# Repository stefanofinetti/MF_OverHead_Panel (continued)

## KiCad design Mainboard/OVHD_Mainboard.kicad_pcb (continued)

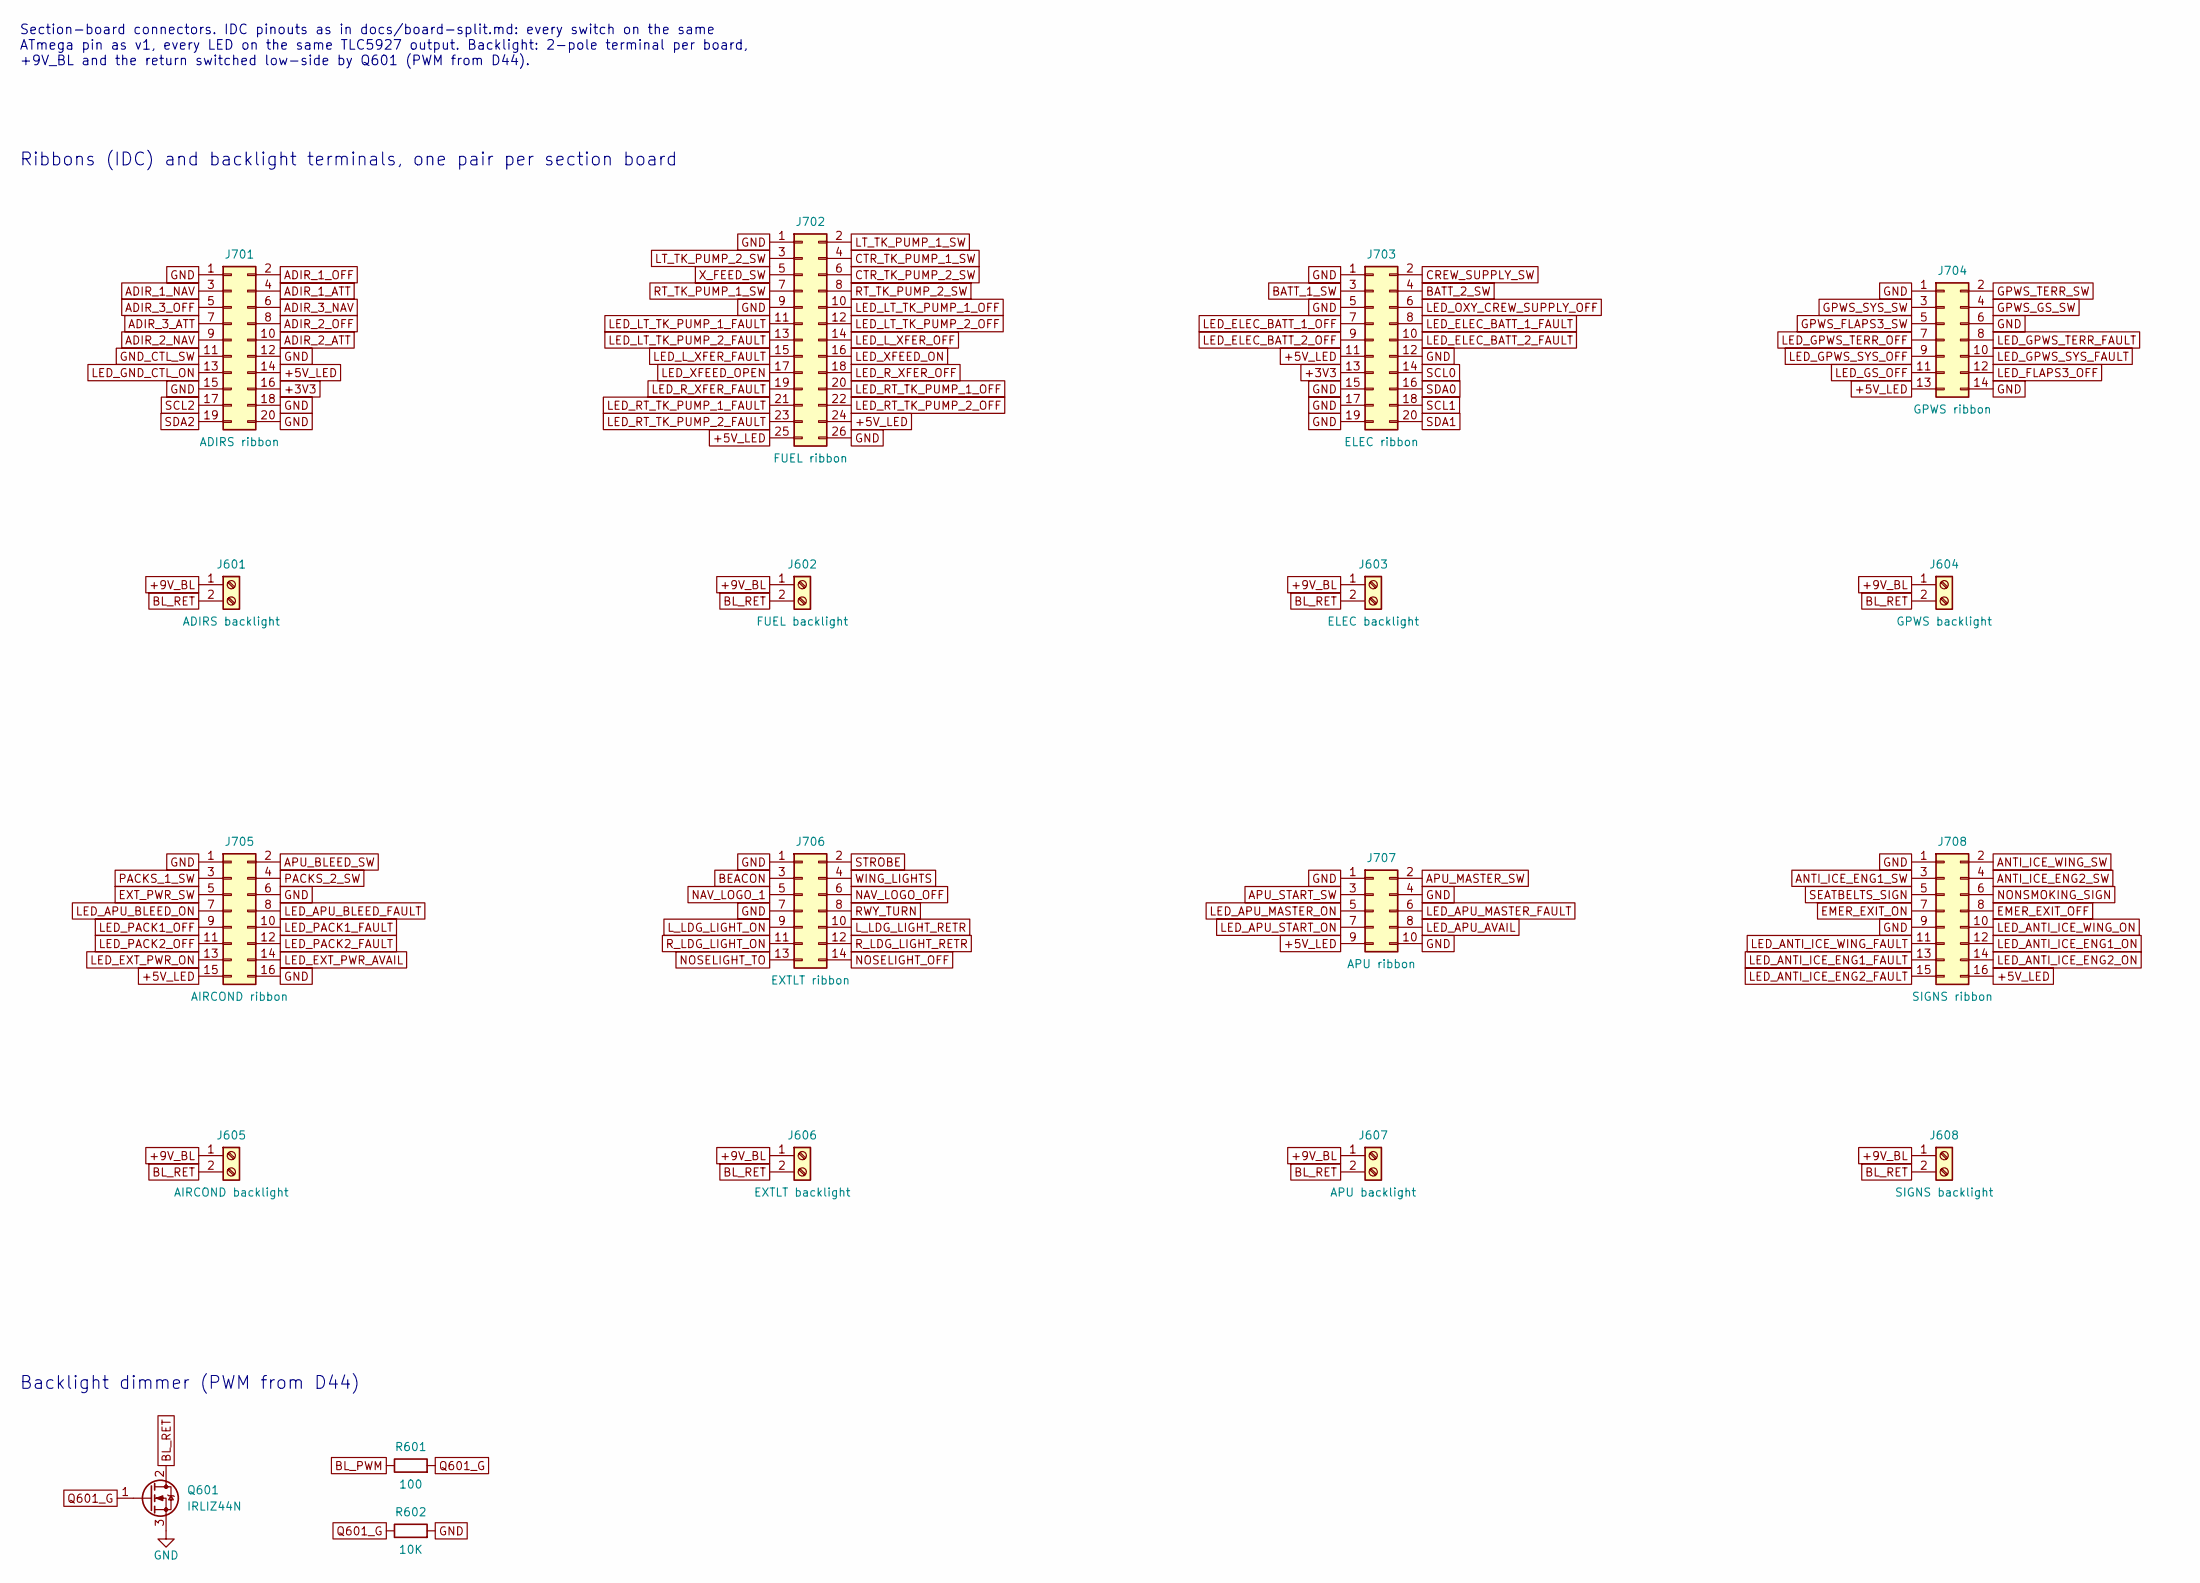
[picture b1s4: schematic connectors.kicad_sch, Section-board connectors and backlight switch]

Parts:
J601: ADIRS backlight; TerminalBlock_Phoenix_PT-1,5-2-3.5-H_1x02_P3.50mm_Horizontal
J602: FUEL backlight; TerminalBlock_Phoenix_PT-1,5-2-3.5-H_1x02_P3.50mm_Horizontal
J603: ELEC backlight; TerminalBlock_Phoenix_PT-1,5-2-3.5-H_1x02_P3.50mm_Horizontal
J604: GPWS backlight; TerminalBlock_Phoenix_PT-1,5-2-3.5-H_1x02_P3.50mm_Horizontal
J605: AIRCOND backlight; TerminalBlock_Phoenix_PT-1,5-2-3.5-H_1x02_P3.50mm_Horizontal
J606: EXTLT backlight; TerminalBlock_Phoenix_PT-1,5-2-3.5-H_1x02_P3.50mm_Horizontal
J607: APU backlight; TerminalBlock_Phoenix_PT-1,5-2-3.5-H_1x02_P3.50mm_Horizontal
J608: SIGNS backlight; TerminalBlock_Phoenix_PT-1,5-2-3.5-H_1x02_P3.50mm_Horizontal
J701: ADIRS ribbon; IDC-Header_2x10_P2.54mm_Vertical
J702: FUEL ribbon; IDC-Header_2x13_P2.54mm_Vertical
J703: ELEC ribbon; IDC-Header_2x10_P2.54mm_Vertical
J704: GPWS ribbon; IDC-Header_2x07_P2.54mm_Vertical
J705: AIRCOND ribbon; IDC-Header_2x08_P2.54mm_Vertical
J706: EXTLT ribbon; IDC-Header_2x07_P2.54mm_Vertical
J707: APU ribbon; IDC-Header_2x05_P2.54mm_Vertical
J708: SIGNS ribbon; IDC-Header_2x08_P2.54mm_Vertical
Q601: IRLIZ44N; TO-220F-3_Horizontal_TabDown
R601: 100; R_1206_3216Metric_Pad1.30x1.75mm_HandSolder
R602: 10K; R_1206_3216Metric_Pad1.30x1.75mm_HandSolder

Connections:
+3V3: J701.16, J703.13; also elsewhere on the board
+5V_LED: J701.14, J702.24, J702.25, J703.11, J704.13, J705.15, J707.9, J708.16; also elsewhere on the board
+9V_BL: J601.1, J602.1, J603.1, J604.1, J605.1, J606.1, J607.1, J608.1; also elsewhere on the board
ADIR_1_ATT: J701.4; also elsewhere on the board
ADIR_1_NAV: J701.3; also elsewhere on the board
ADIR_1_OFF: J701.2; also elsewhere on the board
ADIR_2_ATT: J701.10; also elsewhere on the board
ADIR_2_NAV: J701.9; also elsewhere on the board
ADIR_2_OFF: J701.8; also elsewhere on the board
ADIR_3_ATT: J701.7; also elsewhere on the board
ADIR_3_NAV: J701.6; also elsewhere on the board
ADIR_3_OFF: J701.5; also elsewhere on the board
ANTI_ICE_ENG1_SW: J708.3; also elsewhere on the board
ANTI_ICE_ENG2_SW: J708.4; also elsewhere on the board
ANTI_ICE_WING_SW: J708.2; also elsewhere on the board
APU_BLEED_SW: J705.2; also elsewhere on the board
APU_MASTER_SW: J707.2; also elsewhere on the board
APU_START_SW: J707.3; also elsewhere on the board
BATT_1_SW: J703.3; also elsewhere on the board
BATT_2_SW: J703.4; also elsewhere on the board
BEACON: J706.3; also elsewhere on the board
BL_PWM: R601.1; also elsewhere on the board
BL_RET: J601.2, J602.2, J603.2, J604.2, J605.2, J606.2, J607.2, J608.2, Q601.2 (D)
CREW_SUPPLY_SW: J703.2; also elsewhere on the board
CTR_TK_PUMP_1_SW: J702.4; also elsewhere on the board
CTR_TK_PUMP_2_SW: J702.6; also elsewhere on the board
EMER_EXIT_OFF: J708.8; also elsewhere on the board
EMER_EXIT_ON: J708.7; also elsewhere on the board
EXT_PWR_SW: J705.5; also elsewhere on the board
GND: J701.1, J701.12, J701.15, J701.18, J701.20, J702.1, J702.9, J702.26, J703.1, J703.5, J703.12, J703.15, J703.17, J703.19, J704.1, J704.6, J704.14, J705.1, J705.6, J705.16, J706.1, J706.7, J707.1, J707.4, J707.10, J708.1, J708.9, Q601.3 (S), R602.2; also elsewhere on the board
GND_CTL_SW: J701.11; also elsewhere on the board
GPWS_FLAPS3_SW: J704.5; also elsewhere on the board
GPWS_GS_SW: J704.4; also elsewhere on the board
GPWS_SYS_SW: J704.3; also elsewhere on the board
GPWS_TERR_SW: J704.2; also elsewhere on the board
LED_ANTI_ICE_ENG1_FAULT: J708.13; also elsewhere on the board
LED_ANTI_ICE_ENG1_ON: J708.12; also elsewhere on the board
LED_ANTI_ICE_ENG2_FAULT: J708.15; also elsewhere on the board
LED_ANTI_ICE_ENG2_ON: J708.14; also elsewhere on the board
LED_ANTI_ICE_WING_FAULT: J708.11; also elsewhere on the board
LED_ANTI_ICE_WING_ON: J708.10; also elsewhere on the board
LED_APU_AVAIL: J707.8; also elsewhere on the board
LED_APU_BLEED_FAULT: J705.8; also elsewhere on the board
LED_APU_BLEED_ON: J705.7; also elsewhere on the board
LED_APU_MASTER_FAULT: J707.6; also elsewhere on the board
LED_APU_MASTER_ON: J707.5; also elsewhere on the board
LED_APU_START_ON: J707.7; also elsewhere on the board
LED_ELEC_BATT_1_FAULT: J703.8; also elsewhere on the board
LED_ELEC_BATT_1_OFF: J703.7; also elsewhere on the board
LED_ELEC_BATT_2_FAULT: J703.10; also elsewhere on the board
LED_ELEC_BATT_2_OFF: J703.9; also elsewhere on the board
LED_EXT_PWR_AVAIL: J705.14; also elsewhere on the board
LED_EXT_PWR_ON: J705.13; also elsewhere on the board
LED_FLAPS3_OFF: J704.12; also elsewhere on the board
LED_GND_CTL_ON: J701.13; also elsewhere on the board
LED_GPWS_SYS_FAULT: J704.10; also elsewhere on the board
LED_GPWS_SYS_OFF: J704.9; also elsewhere on the board
LED_GPWS_TERR_FAULT: J704.8; also elsewhere on the board
LED_GPWS_TERR_OFF: J704.7; also elsewhere on the board
LED_GS_OFF: J704.11; also elsewhere on the board
LED_LT_TK_PUMP_1_FAULT: J702.11; also elsewhere on the board
LED_LT_TK_PUMP_1_OFF: J702.10; also elsewhere on the board
LED_LT_TK_PUMP_2_FAULT: J702.13; also elsewhere on the board
LED_LT_TK_PUMP_2_OFF: J702.12; also elsewhere on the board
LED_L_XFER_FAULT: J702.15; also elsewhere on the board
LED_L_XFER_OFF: J702.14; also elsewhere on the board
LED_OXY_CREW_SUPPLY_OFF: J703.6; also elsewhere on the board
LED_PACK1_FAULT: J705.10; also elsewhere on the board
LED_PACK1_OFF: J705.9; also elsewhere on the board
LED_PACK2_FAULT: J705.12; also elsewhere on the board
LED_PACK2_OFF: J705.11; also elsewhere on the board
LED_RT_TK_PUMP_1_FAULT: J702.21; also elsewhere on the board
LED_RT_TK_PUMP_1_OFF: J702.20; also elsewhere on the board
LED_RT_TK_PUMP_2_FAULT: J702.23; also elsewhere on the board
LED_RT_TK_PUMP_2_OFF: J702.22; also elsewhere on the board
LED_R_XFER_FAULT: J702.19; also elsewhere on the board
LED_R_XFER_OFF: J702.18; also elsewhere on the board
LED_XFEED_ON: J702.16; also elsewhere on the board
LED_XFEED_OPEN: J702.17; also elsewhere on the board
LT_TK_PUMP_1_SW: J702.2; also elsewhere on the board
LT_TK_PUMP_2_SW: J702.3; also elsewhere on the board
L_LDG_LIGHT_ON: J706.9; also elsewhere on the board
L_LDG_LIGHT_RETR: J706.10; also elsewhere on the board
NAV_LOGO_1: J706.5; also elsewhere on the board
NAV_LOGO_OFF: J706.6; also elsewhere on the board
NONSMOKING_SIGN: J708.6; also elsewhere on the board
NOSELIGHT_OFF: J706.14; also elsewhere on the board
NOSELIGHT_TO: J706.13; also elsewhere on the board
PACKS_1_SW: J705.3; also elsewhere on the board
PACKS_2_SW: J705.4; also elsewhere on the board
Q601_G: Q601.1 (G), R601.2, R602.1
RT_TK_PUMP_1_SW: J702.7; also elsewhere on the board
RT_TK_PUMP_2_SW: J702.8; also elsewhere on the board
RWY_TURN: J706.8; also elsewhere on the board
R_LDG_LIGHT_ON: J706.11; also elsewhere on the board
R_LDG_LIGHT_RETR: J706.12; also elsewhere on the board
SCL0: J703.14; also elsewhere on the board
SCL1: J703.18; also elsewhere on the board
SCL2: J701.17; also elsewhere on the board
SDA0: J703.16; also elsewhere on the board
SDA1: J703.20; also elsewhere on the board
SDA2: J701.19; also elsewhere on the board
SEATBELTS_SIGN: J708.5; also elsewhere on the board
STROBE: J706.2; also elsewhere on the board
WING_LIGHTS: J706.4; also elsewhere on the board
X_FEED_SW: J702.5; also elsewhere on the board

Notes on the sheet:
Ribbons (IDC) and backlight terminals, one pair per section board
Section-board connectors. IDC pinouts as in docs/board-split.md: every switch on the same ATmega pin as v1, every LED on the same TLC5927 output. Backlight: 2-pole terminal per board, +9V_BL and the return switched low-side by Q601 (PWM from D44).
Backlight dimmer (PWM from D44)

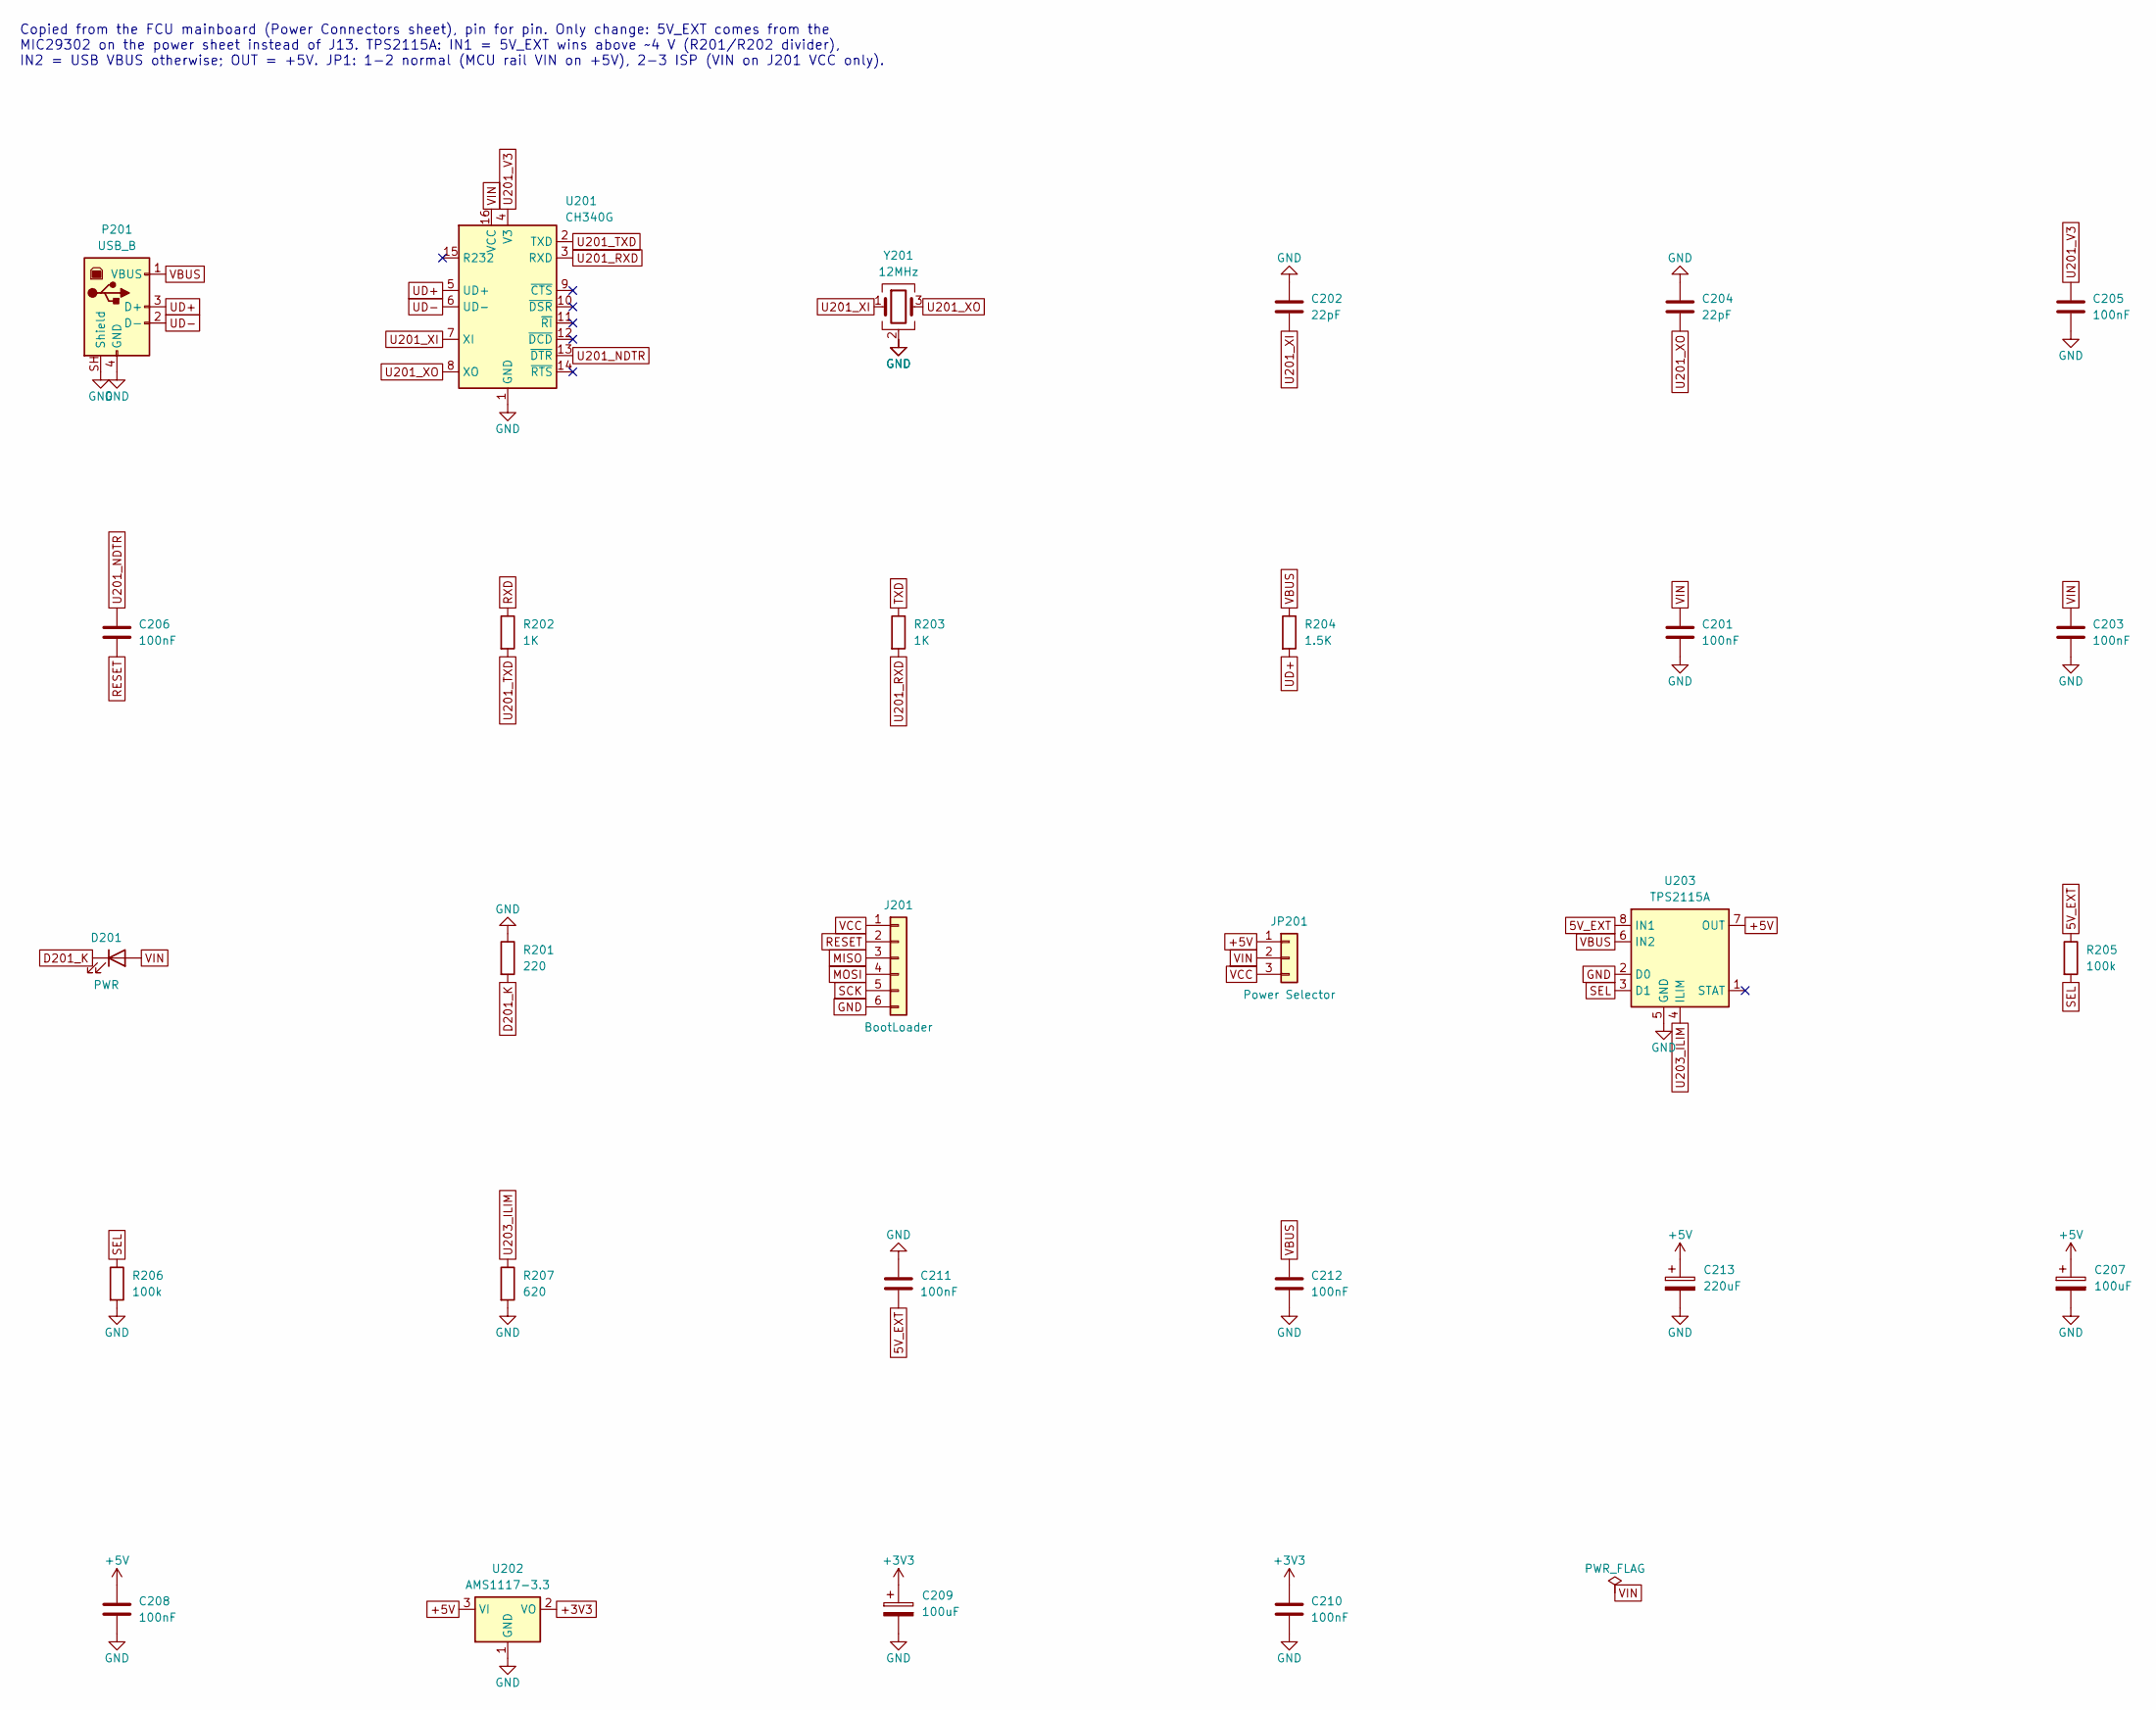
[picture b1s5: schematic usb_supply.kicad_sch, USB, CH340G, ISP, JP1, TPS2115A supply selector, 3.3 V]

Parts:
C201, C203, C205, C206, C208, C210, C211, C212: 100nF; C_1206_3216Metric_Pad1.33x1.80mm_HandSolder
C202, C204: 22pF; C_1206_3216Metric_Pad1.33x1.80mm_HandSolder
C207, C209: 100uF; C_Elec_6.3x7.7
C213: 220uF; C_Elec_6.3x7.7
D201: PWR; LED_1206_3216Metric_Pad1.42x1.75mm_HandSolder
J201: BootLoader; PinHeader_1x06_P2.54mm_Vertical
JP201: Power Selector; PinHeader_1x03_P2.54mm_Vertical
P201: USB_B; USB_B_OST_USB-B1HSxx_Horizontal
R201: 220; R_1206_3216Metric_Pad1.30x1.75mm_HandSolder
R202, R203: 1K; R_1206_3216Metric_Pad1.30x1.75mm_HandSolder
R204: 1.5K; R_1206_3216Metric_Pad1.30x1.75mm_HandSolder
R205, R206: 100k; R_1206_3216Metric_Pad1.30x1.75mm_HandSolder
R207: 620; R_1206_3216Metric_Pad1.30x1.75mm_HandSolder
U201: CH340G; SOIC-16_3.9x9.9mm_P1.27mm
U202: AMS1117-3.3; SOT-223-3_TabPin2
U203: TPS2115A; TSSOP-8_4.4x3mm_P0.65mm
Y201: 12MHz; Crystal_SMD_EuroQuartz_MQ-4Pin_7.0x5.0mm_HandSoldering

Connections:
5V_EXT: C211.2, R205.1, U203.8 (IN1); also elsewhere on the board
+3V3: C209.1, C210.1, U202.2 (VO); also elsewhere on the board
+5V: C207.1, C208.1, C213.1, JP201.1, U202.3 (VI), U203.7 (OUT); also elsewhere on the board
D201_K: D201.1 (K), R201.2
GND: C201.2, C202.1, C203.2, C204.1, C205.2, C207.2, C208.2, C209.2, C210.2, C211.1, C212.2, C213.2, J201.6, P201.4 (GND), P201.SH (Shield), R201.1, R206.2, R207.2, U201.1 (GND), U202.1 (GND), U203.2 (D0), U203.5 (GND), Y201.2 (G), Y201.4 (G); also elsewhere on the board
MISO: J201.3; also elsewhere on the board
MOSI: J201.4; also elsewhere on the board
RESET: C206.2, J201.2; also elsewhere on the board
RXD: R202.1; also elsewhere on the board
SCK: J201.5; also elsewhere on the board
SEL: R205.2, R206.1, U203.3 (D1)
TXD: R203.1; also elsewhere on the board
U201_NDTR: C206.1, U201.13 (~DTR)
U201_RXD: R203.2, U201.3 (RXD)
U201_TXD: R202.2, U201.2 (TXD)
U201_V3: C205.1, U201.4 (V3)
U201_XI: C202.2, U201.7 (XI), Y201.1
U201_XO: C204.2, U201.8 (XO), Y201.3
U203_ILIM: R207.1, U203.4 (ILIM)
UD+: P201.3 (D+), R204.2, U201.5 (UD+)
UD-: P201.2 (D-), U201.6 (UD-)
VBUS: C212.1, P201.1 (VBUS), R204.1, U203.6 (IN2)
VCC: J201.1, JP201.3
VIN: C201.1, C203.1, D201.2 (A), JP201.2, U201.16 (VCC); also elsewhere on the board

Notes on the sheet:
Copied from the FCU mainboard (Power Connectors sheet), pin for pin. Only change: 5V_EXT comes from the MIC29302 on the power sheet instead of J13. TPS2115A: IN1 = 5V_EXT wins above ~4 V (R201/R202 divider), IN2 = USB VBUS otherwise; OUT = +5V. JP1: 1-2 normal (MCU rail VIN on +5V), 2-3 ISP (VIN on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

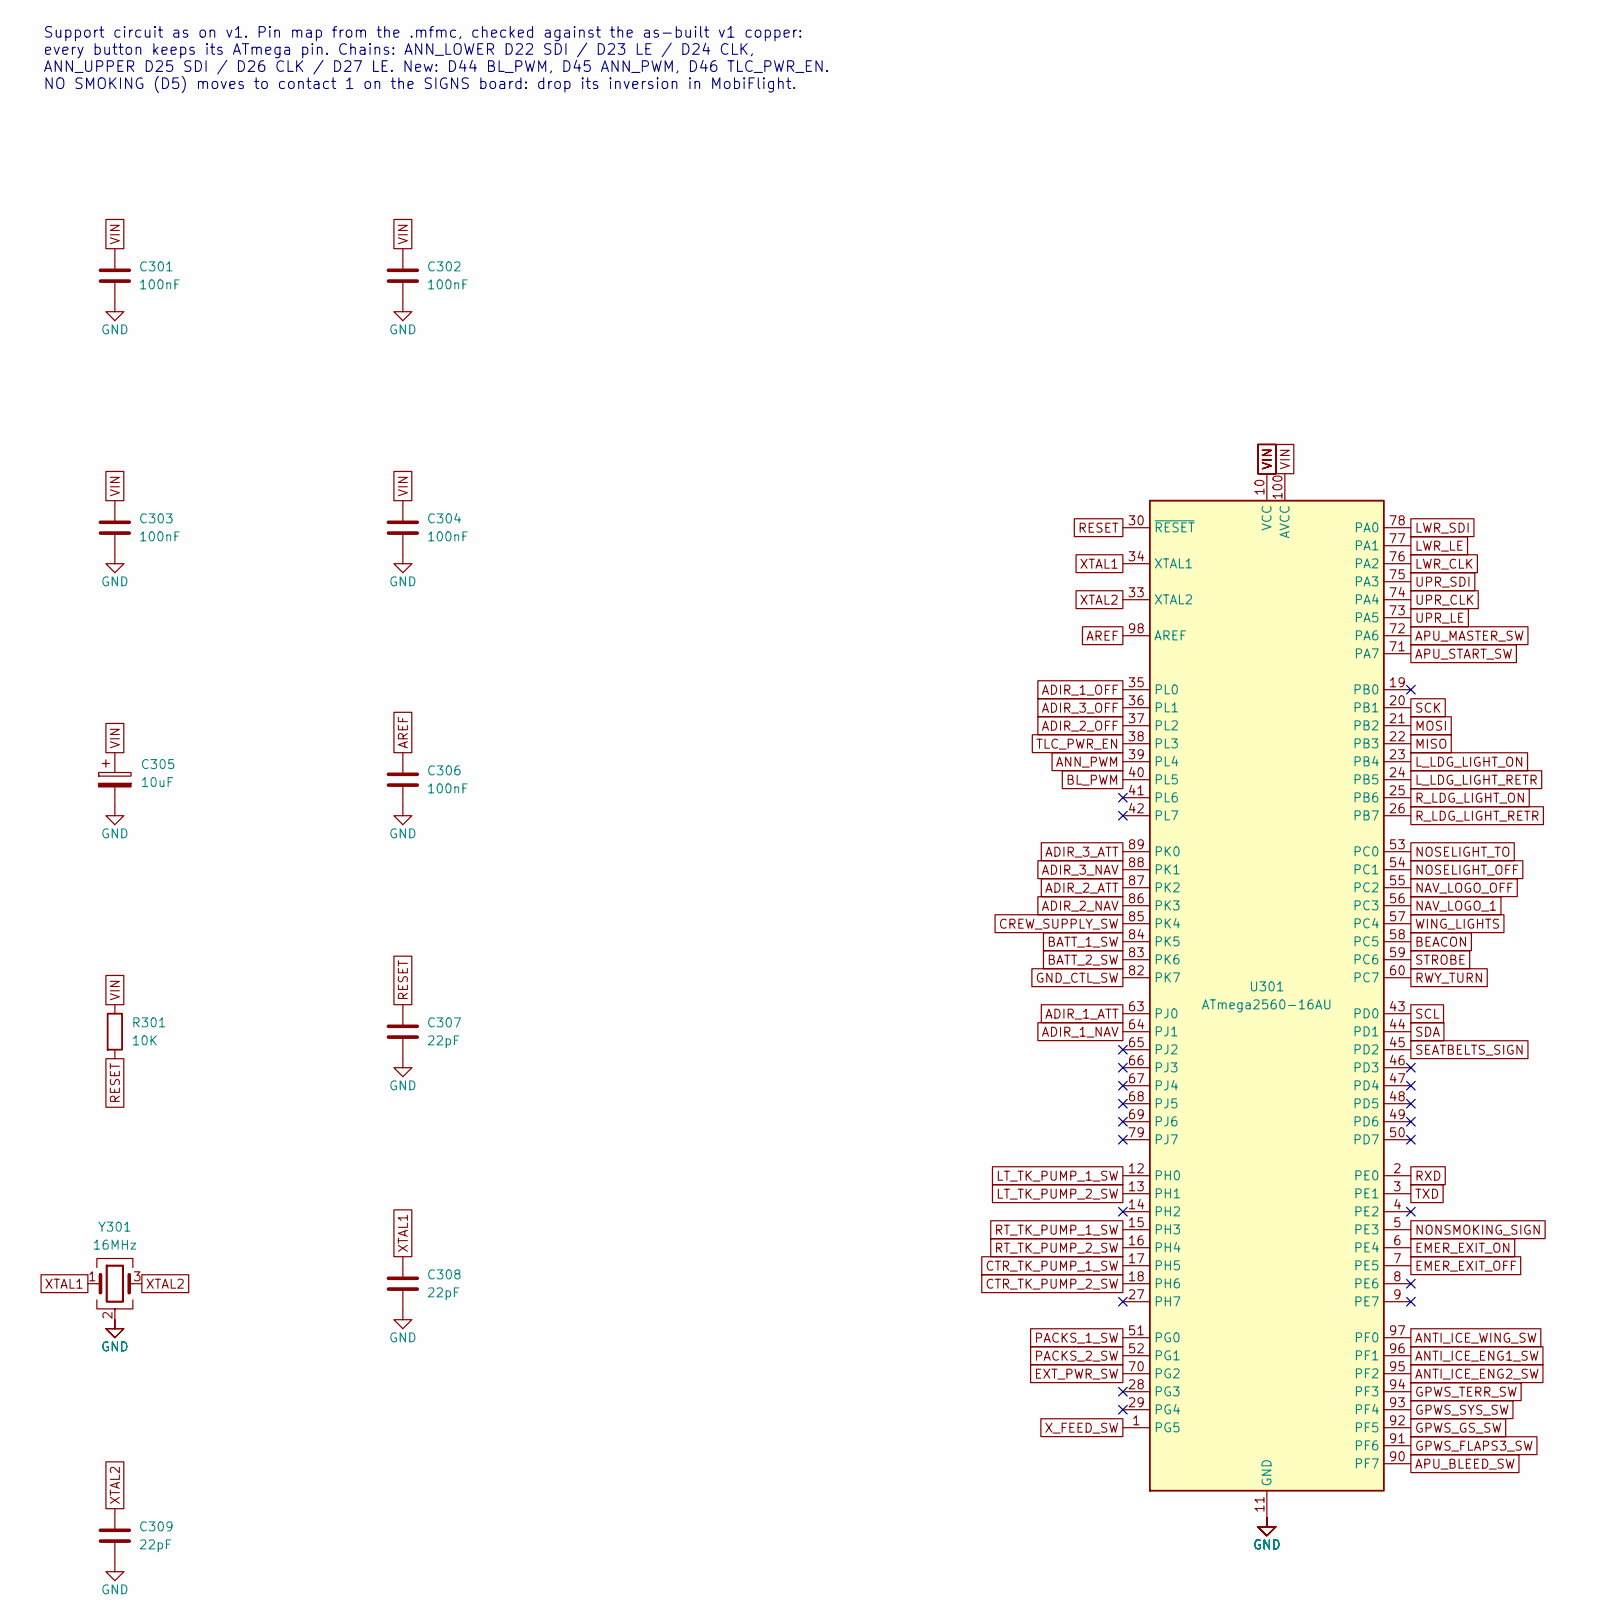
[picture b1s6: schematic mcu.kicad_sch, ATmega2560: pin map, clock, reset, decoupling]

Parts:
C301, C302, C303, C304, C306: 100nF; C_1206_3216Metric_Pad1.33x1.80mm_HandSolder
C305: 10uF; CP_Elec_4x5.4
C307, C308, C309: 22pF; C_1206_3216Metric_Pad1.33x1.80mm_HandSolder
R301: 10K; R_1206_3216Metric_Pad1.30x1.75mm_HandSolder
U301: ATmega2560-16AU; TQFP-100_14x14mm_P0.5mm
Y301: 16MHz; Crystal_SMD_EuroQuartz_MQ-4Pin_7.0x5.0mm_HandSoldering

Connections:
ADIR_1_ATT: U301.63 (PJ0); also elsewhere on the board
ADIR_1_NAV: U301.64 (PJ1); also elsewhere on the board
ADIR_1_OFF: U301.35 (PL0); also elsewhere on the board
ADIR_2_ATT: U301.87 (PK2); also elsewhere on the board
ADIR_2_NAV: U301.86 (PK3); also elsewhere on the board
ADIR_2_OFF: U301.37 (PL2); also elsewhere on the board
ADIR_3_ATT: U301.89 (PK0); also elsewhere on the board
ADIR_3_NAV: U301.88 (PK1); also elsewhere on the board
ADIR_3_OFF: U301.36 (PL1); also elsewhere on the board
ANN_PWM: U301.39 (PL4); also elsewhere on the board
ANTI_ICE_ENG1_SW: U301.96 (PF1); also elsewhere on the board
ANTI_ICE_ENG2_SW: U301.95 (PF2); also elsewhere on the board
ANTI_ICE_WING_SW: U301.97 (PF0); also elsewhere on the board
APU_BLEED_SW: U301.90 (PF7); also elsewhere on the board
APU_MASTER_SW: U301.72 (PA6); also elsewhere on the board
APU_START_SW: U301.71 (PA7); also elsewhere on the board
AREF: C306.1, U301.98 (AREF)
BATT_1_SW: U301.84 (PK5); also elsewhere on the board
BATT_2_SW: U301.83 (PK6); also elsewhere on the board
BEACON: U301.58 (PC5); also elsewhere on the board
BL_PWM: U301.40 (PL5); also elsewhere on the board
CREW_SUPPLY_SW: U301.85 (PK4); also elsewhere on the board
CTR_TK_PUMP_1_SW: U301.17 (PH5); also elsewhere on the board
CTR_TK_PUMP_2_SW: U301.18 (PH6); also elsewhere on the board
EMER_EXIT_OFF: U301.7 (PE5); also elsewhere on the board
EMER_EXIT_ON: U301.6 (PE4); also elsewhere on the board
EXT_PWR_SW: U301.70 (PG2); also elsewhere on the board
GND: C301.2, C302.2, C303.2, C304.2, C305.2, C306.2, C307.2, C308.2, C309.2, U301.11 (GND), U301.32 (GND), U301.62 (GND), U301.81 (GND), U301.99 (GND), Y301.2 (G), Y301.4 (G); also elsewhere on the board
GND_CTL_SW: U301.82 (PK7); also elsewhere on the board
GPWS_FLAPS3_SW: U301.91 (PF6); also elsewhere on the board
GPWS_GS_SW: U301.92 (PF5); also elsewhere on the board
GPWS_SYS_SW: U301.93 (PF4); also elsewhere on the board
GPWS_TERR_SW: U301.94 (PF3); also elsewhere on the board
LT_TK_PUMP_1_SW: U301.12 (PH0); also elsewhere on the board
LT_TK_PUMP_2_SW: U301.13 (PH1); also elsewhere on the board
LWR_CLK: U301.76 (PA2); also elsewhere on the board
LWR_LE: U301.77 (PA1); also elsewhere on the board
LWR_SDI: U301.78 (PA0); also elsewhere on the board
L_LDG_LIGHT_ON: U301.23 (PB4); also elsewhere on the board
L_LDG_LIGHT_RETR: U301.24 (PB5); also elsewhere on the board
MISO: U301.22 (PB3); also elsewhere on the board
MOSI: U301.21 (PB2); also elsewhere on the board
NAV_LOGO_1: U301.56 (PC3); also elsewhere on the board
NAV_LOGO_OFF: U301.55 (PC2); also elsewhere on the board
NONSMOKING_SIGN: U301.5 (PE3); also elsewhere on the board
NOSELIGHT_OFF: U301.54 (PC1); also elsewhere on the board
NOSELIGHT_TO: U301.53 (PC0); also elsewhere on the board
PACKS_1_SW: U301.51 (PG0); also elsewhere on the board
PACKS_2_SW: U301.52 (PG1); also elsewhere on the board
RESET: C307.1, R301.2, U301.30 (~RESET); also elsewhere on the board
RT_TK_PUMP_1_SW: U301.15 (PH3); also elsewhere on the board
RT_TK_PUMP_2_SW: U301.16 (PH4); also elsewhere on the board
RWY_TURN: U301.60 (PC7); also elsewhere on the board
RXD: U301.2 (PE0); also elsewhere on the board
R_LDG_LIGHT_ON: U301.25 (PB6); also elsewhere on the board
R_LDG_LIGHT_RETR: U301.26 (PB7); also elsewhere on the board
SCK: U301.20 (PB1); also elsewhere on the board
SCL: U301.43 (PD0); also elsewhere on the board
SDA: U301.44 (PD1); also elsewhere on the board
SEATBELTS_SIGN: U301.45 (PD2); also elsewhere on the board
STROBE: U301.59 (PC6); also elsewhere on the board
TLC_PWR_EN: U301.38 (PL3); also elsewhere on the board
TXD: U301.3 (PE1); also elsewhere on the board
UPR_CLK: U301.74 (PA4); also elsewhere on the board
UPR_LE: U301.73 (PA5); also elsewhere on the board
UPR_SDI: U301.75 (PA3); also elsewhere on the board
VIN: C301.1, C302.1, C303.1, C304.1, C305.1, R301.1, U301.10 (VCC), U301.31 (VCC), U301.61 (VCC), U301.80 (VCC), U301.100 (AVCC); also elsewhere on the board
WING_LIGHTS: U301.57 (PC4); also elsewhere on the board
XTAL1: C308.1, U301.34 (XTAL1), Y301.1
XTAL2: C309.1, U301.33 (XTAL2), Y301.3
X_FEED_SW: U301.1 (PG5); also elsewhere on the board

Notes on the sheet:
Support circuit as on v1. Pin map from the .mfmc, checked against the as-built v1 copper: every button keeps its ATmega pin. Chains: ANN_LOWER D22 SDI / D23 LE / D24 CLK, ANN_UPPER D25 SDI / D26 CLK / D27 LE. New: D44 BL_PWM, D45 ANN_PWM, D46 TLC_PWR_EN. NO SMOKING (D5) moves to contact 1 on the SI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

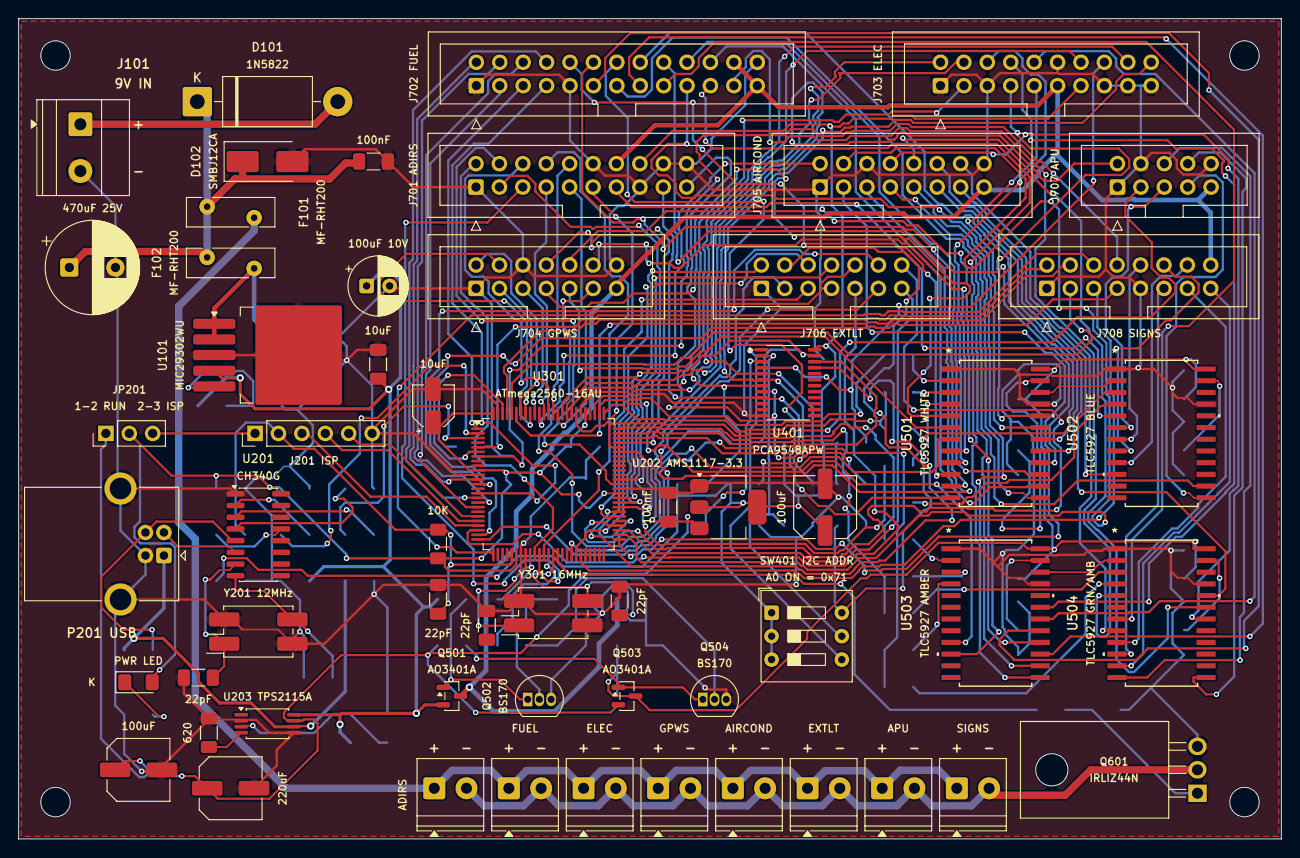
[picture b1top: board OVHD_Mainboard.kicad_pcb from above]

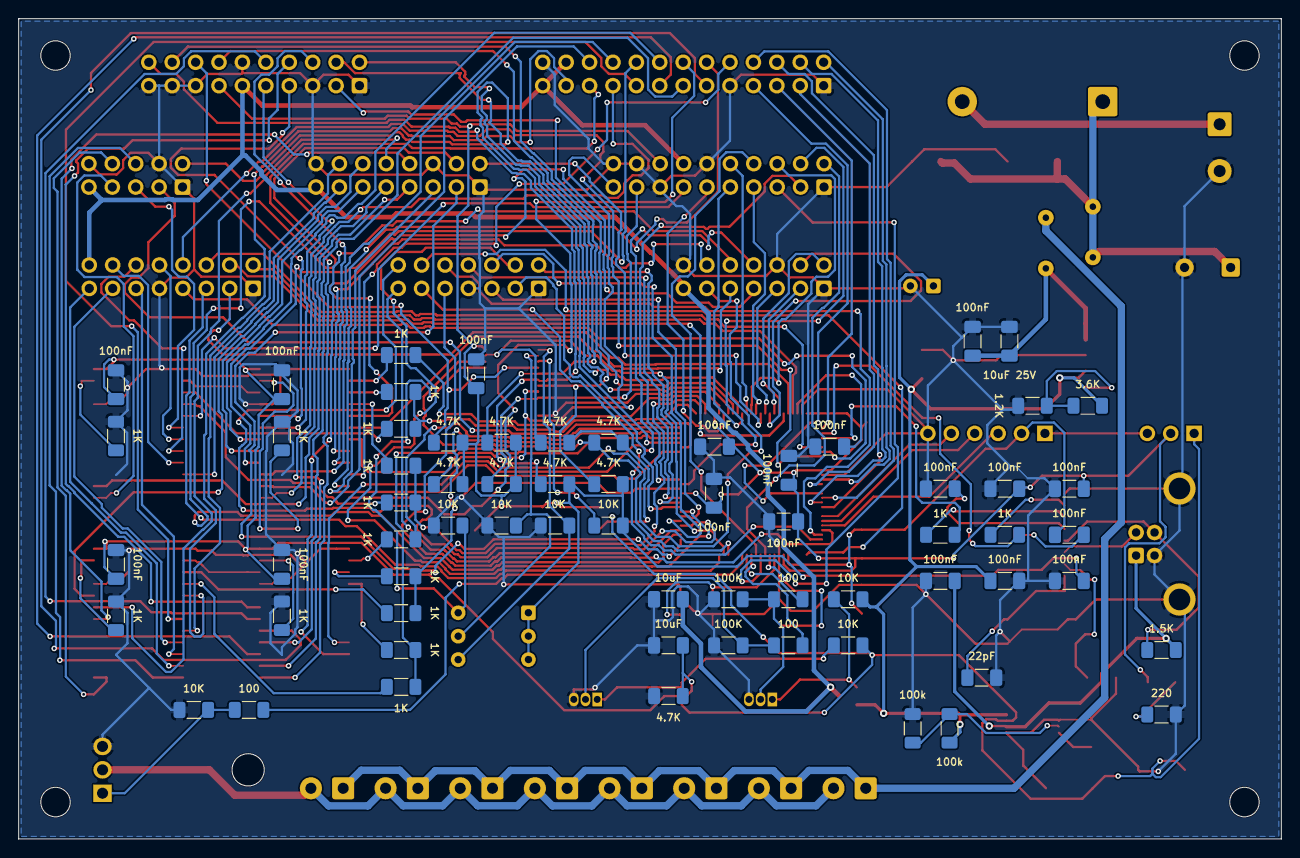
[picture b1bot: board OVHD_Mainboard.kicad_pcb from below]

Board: 2 copper layers, 137.0 x 89.0 mm, 127 parts (65 on the bottom side), 170 nets.

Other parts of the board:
H1, H2, H3, H4: MountingHole_3.2mm_M3
